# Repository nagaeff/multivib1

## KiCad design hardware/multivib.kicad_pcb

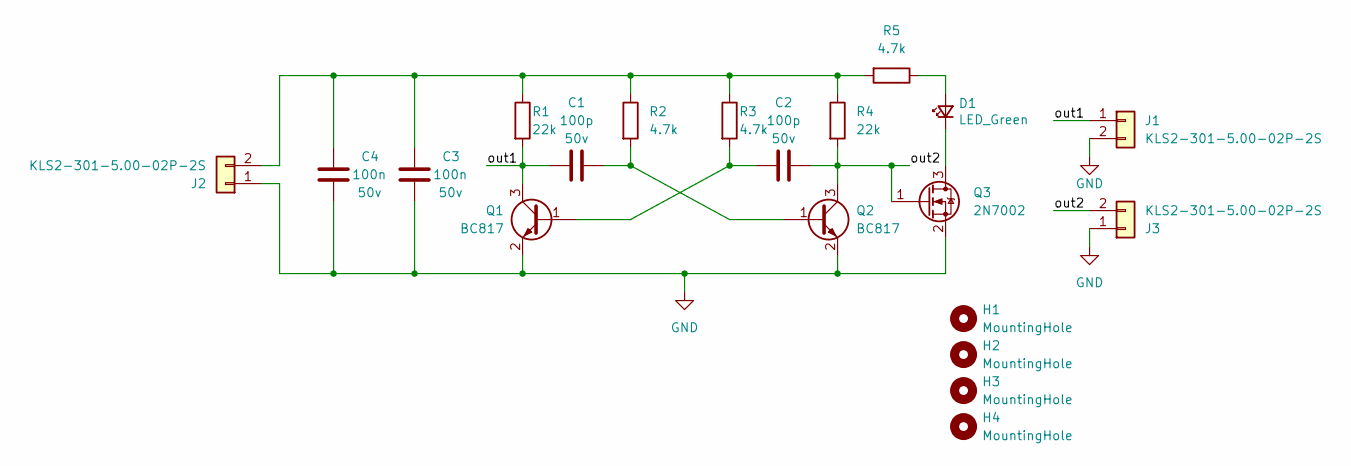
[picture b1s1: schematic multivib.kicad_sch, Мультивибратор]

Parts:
C1, C2: 100p; C_0805_2012Metric; Voltage 50v; lcsc C1790
C3, C4: 100n; C_0805_2012Metric; Voltage 50v; lcsc C49678
D1: LED_Green; LED_0805_2012Metric; lcsc C2297
H1, H2, H3, H4: MountingHole; MountingHole_2.2mm_M2_DIN965
J1, J2, J3: KLS2-301-5.00-02P-2S; lcsc C699495
Q1, Q2: BC817; SOT-23; lcsc C85078
Q3: 2N7002; SOT-23; lcsc C8545
R1, R4: 22k; R_0805_2012Metric_Pad1.20x1.40mm_HandSolder; lcsc C17560
R2, R3, R5: 4.7k; R_0805_2012Metric_Pad1.20x1.40mm_HandSolder; lcsc C17673

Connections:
/out1: C1.2, J1.1, Q1.3 (C), R1.2
/out2: C2.1, J3.2, Q2.3 (C), Q3.1 (G), R4.2
GND: C3.2, C4.2, J1.2, J2.1, J3.1, Q1.2 (E), Q2.2 (E), Q3.2 (S)
unnamed: C1.1, Q2.1 (B), R2.2
unnamed: C2.2, Q1.1 (B), R3.2
unnamed: C3.1, C4.1, J2.2, R1.1, R2.1, R3.1, R4.1, R5.2
unnamed: D1.1 (K), Q3.3 (D)
unnamed: D1.2 (A), R5.1

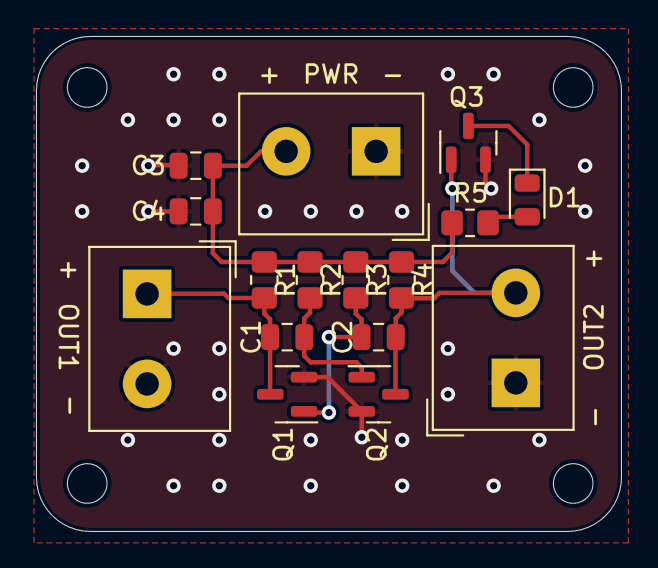
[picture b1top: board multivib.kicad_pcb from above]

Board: 2 copper layers, 32.5 x 27.5 mm, 20 parts (0 on the bottom side), 8 nets.

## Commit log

2022-05-20 добавлены компоненты на плату
2022-05-27 плата
2022-05-27 работа с разводкой
2022-05-30 почти готово
2022-05-30 готово
